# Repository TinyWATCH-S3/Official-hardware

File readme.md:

# TinyWATCH-S3 Official Hardware

In this repository, you will find all of the KiCAD design files for the official Unexpected Maker TinyWATCH-S3

**The current release version of the TinyWATCH S3 hardware is revision P10.**

Please note that the license for these design files is the CERN Open Hardware Licence v1.2, which requires any use of these design files to be also kept fully open source under the same license.

So though you are free to use these files in your own projects, and even commercialise them, the "thing" you make must be open source and shared with the community.

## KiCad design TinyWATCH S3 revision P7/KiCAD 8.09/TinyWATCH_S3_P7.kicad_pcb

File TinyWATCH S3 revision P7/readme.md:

# TinyWATCH-S3 revision P7

I've made my best efforts to ensure consistency between the PCB layout and Schematic in terms of component values and packages.

Many footprints in the design reference non-standard (library) footprints, and I don't offer a library for them as they are already embedded in PCB layout anyway. 

If you do find any other inconsistencies, please create a PR, or raise an issue, thanks :)

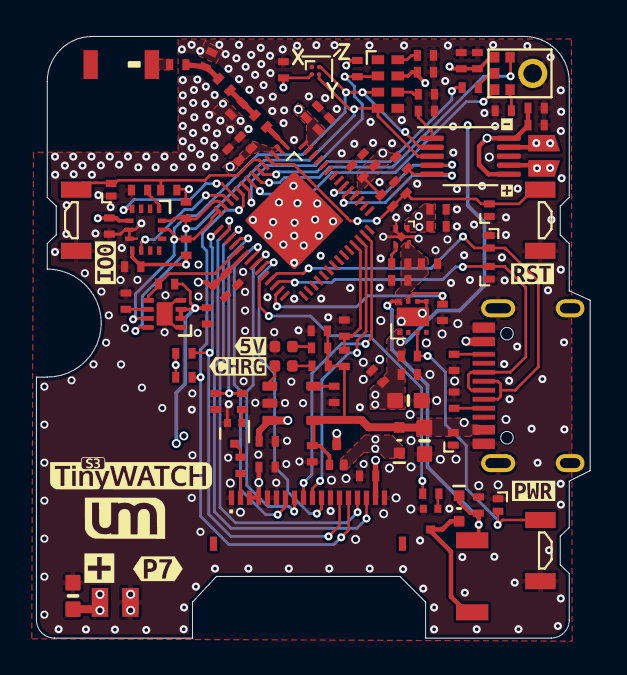
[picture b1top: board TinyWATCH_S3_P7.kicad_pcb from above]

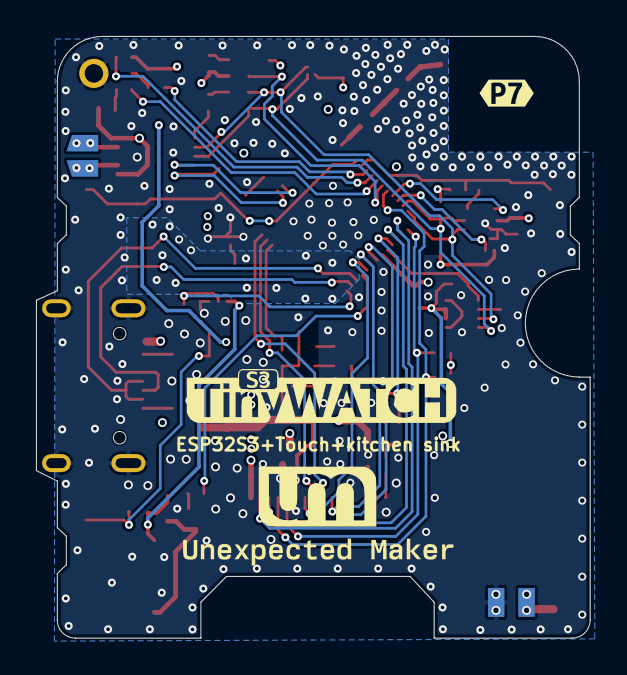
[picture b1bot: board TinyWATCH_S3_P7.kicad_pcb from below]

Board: 4 copper layers, 30.8 x 33.4 mm, 115 parts (3 on the bottom side), 60 nets.

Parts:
AF1: 3.6pF; _0402_SRN
AF2: 1.5nH; _0402_SRN
AF3: 2.4nH; _0402_SRN
BAT1: LIPO; HapticMotor_Solder_Pads
C1, C4, C6, C8, C10, C11, C12, C13, C14, C16, C17, C19, C22, C23, C31: 0.1uF; _0402_SRN
C2, C3, C9, C15, C18, C20, C24, C25, C27, C30, C33: 1uF; _0402_SRN
C5: 1.0pF; _0402_SRN
C7, C21, C28: 10uF; _0603MP
C26: 220pF; _0402_SRN
C29, C32, C34: 2.2uF; _0402_SRN
CHRG2: TP4065-4.2V-SOT25-R; SOT23-5-SML2
D1, D2, D4, D9, D10, D11: D_TVS; TVS X1-DFN1006-2-BEST
D3: ORANGE; LED_0402_1005Metric
D5: DIODE-SCHOTTKYWIDE; SOD-523-MSK4010
D6: DIODESOD-123; SOD-523-MSK4010
D8: RED; LED_0402_1005Metric
IC2: ESP32-S3REV0-SILICON; QFN56-ESP32-S3-PROD-THIN
IC3: XC6194AA03ER-G; XC6194BANNERG
IC4: ICS_43434; ICS43434
J1: Conn_01x02_Pin; HapticMotor_Solder_Pads
J2: USB_C; USB-C-16P-LESSPASTE-2-FIxed
J3: Conn_01x18_Pin; JUSHUO AFH34-S18FIA-1H
L1: 3.3nH; _0402_SRN
Q1: MMBT2222; SOT-723
Q2: 600mA/40V; SOT-723
R1, R9, R11, R15: 5.1K; _0402_SRN
R2: 2K; _0402_SRN
R3, R16: 3K3; _0402_SRN
R4, R5, R6, R12, R25, R28, R29, R33: 10K; _0402_SRN
R7, R8, R10, R13, R14, R17, R18, R21, R22, R23, R30: 100K; _0402_SRN
R19: 1K; _0402_SRN
R20: 22; _0402_SRN
R26: 68; _0402_SRN
R27: 1k2; _0402_SRN
SP1: Speaker; MagneticBuzzer_KLJ-4020
SW1, SW3, SW5: SW_Push; SW_SPST_B3U-3000P
T1, T1#2: Tab
T3: P-FET; SOT723
U1: RV-3028-C7-32.768KHZ; IC_RV-3028-C7-32.768KHZ-1PPM-TA-QA
U2: MMC5603NJL; WLP-4_0.83x0.83mm_P0.4mm
U3: NCP167BMX330TBG; VREG_NCP170AMX300TCG
U4: MAX17048G+T10; MAX17048G_T10_SON50P200X200X80-9N
U5: DRV2605LDGSR; VSSOP-10_3x3mm_P0.5mm
U$1: BMI270
U$13: FRACTUS_FR05-S1-N-0-102-LEAN; ANT_2450AT18B100E
U$88: UM_LOGONEW_SMALLER; UM_LOGO_NEW_TINY
U$88#2: UM_LOGONEW_SMALLER; UM_LOGO_NEW_SMALL
kibuzzard-64F95D11: G***; kibuzzard-64F95D11
kibuzzard-64F95D18: G***; kibuzzard-64F95D18
kibuzzard-65BEEB54: G***; kibuzzard-65BEEB54
kibuzzard-65BEEBBF: G***; kibuzzard-65BEEBBF
kibuzzard-65BF212E: G***; kibuzzard-65BF212E
kibuzzard-664EFB11: G***; kibuzzard-664EFB11
kibuzzard-664EFB60: G***; kibuzzard-664EFB60
kibuzzard-6518A76D: G***; kibuzzard-6518A76D
kibuzzard-6518A765: G***; kibuzzard-6518A765
kibuzzard-6534A245: G***; kibuzzard-6534A245
kibuzzard-664315DB: G***; kibuzzard-664315DB

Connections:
3.3V: C1.1, C2.1, C8.1, C9.1, C11.1, C12.1, C13.1, C14.1, C15.1, C16.1, C17.1, C18.1, C19.1, C20.1, C24.1, C26.1, C31.1, C33.1, C34.1, IC2.2 (VDDA3P3_1), IC2.3 (VDDA3P3_2), IC2.20 (VDD3P3_RTC), IC2.46 (VDD3P3_CPU), IC2.55 (VDDA_2), IC2.56 (VDDA_1), IC4.5 (VDD), J3.3, J3.4, J3.17, R4.1, R5.1, R7.1, R10.1, R14.1, R18.1, R28.1, R29.1, U2.B1 (VDD), U3.1 (OUT), U5.6 (VDD/NC), U5.10 (VDD), U$1.5 (VDDIO), U$1.8 (VDD)
/ANT: AF3.2, U$13.1
/ANT_FREQ: AF1.2, AF2.2, AF3.1
/ANT_MATCH: AF1.1, C5.2, L1.1
/BMA_INT1: IC2.11 (IO6), U$1.4 (INT1)
/BMA_INT2: IC2.12 (IO7), U$1.9 (INT2)
/BMI_ADR: R23.1, U$1.1 (SDO)
/BUZZ: D6.A, Q2.3 (C), SP1.-
/BUZZ_T: Q2.1 (B), R27.1
/CC1: J2.A5 (CC1), R11.2
/CC2: J2.B5 (CC2), R9.2
/D+: D2.2 (A2), IC2.26 (IO20/USB_D+), J2.A6 (D+), J2.B6 (D+)
/D-: D4.2 (A2), IC2.25 (IO19/USB_D-), J2.A7 (D-), J2.B7 (D-)
/HAP_EN: IC2.47 (MTDI), R18.2, U5.5 (EN)
/HAP_TRIG: IC2.48 (MTMS), U5.4 (IN/TRIG)
/IO0: D10.2 (A2), IC2.5 (IO0), R10.2, SW3.2
/IO5_SDA2: IC2.10 (IO5), J3.14, R29.2
/IO10_SCL2: IC2.15 (IO10), J3.13, R28.2
/IO18_BUZZ: IC2.24 (IO18), R27.2
/LDO_EN: R30.2, U3.3 (EN)
/LEDK: J3.2, R20.2
/LNA_IN: IC2.1 (LNA_IN), L1.2
/MIC_BCLK: IC2.7 (IO2), IC4.4 (BCLK)
/MIC_DATA: IC2.6 (IO1), R26.2
/MIC_SELECT: IC4.2 (SELECT), R13.2
/MIC_WS: IC2.8 (IO3), IC4.1 (WS)
/ON-SW: D9.2 (A2), IC3.3 (SW), R33.1, SW5.1
/OUT+: J1.1, U5.7 (OUT+)
/OUT-: J1.2, U5.9 (OUT-)
/PROG: CHRG2.5 (PROG), R16.1
/PWR-SHUTDOWN: IC2.27 (IO21), IC3.7 (SHDN), R25.1
/RESET: C3.1, D11.2 (A2), IC2.4 (CHIP_PU), R14.2, SW1.1
/RTC_EVI: R6.1, U1.8 (EVI)
/SCL: IC2.14 (IO9), R5.2, U1.3 (SCL), U2.A2 (SCL), U4.7 (SCL), U5.2 (SCL), U$1.13 (SCX)
/SDA: IC2.13 (IO8), R4.2, U1.4 (SDA), U2.B2 (SDA), U4.8 (SDA), U5.3 (SDA), U$1.14 (SDX)
/SPI_MO: IC2.40 (IO35), J3.10
/SPI_SCK: IC2.41 (IO36), J3.9
/STAT: CHRG2.1 (STAT), D3.P$2 (2)
/TCH_INT: IC2.16 (IO11), J3.16
/TCH_RST: IC2.17 (IO12), J3.15
/TFT_BACKLIGHT: IC2.18 (IO13), R12.1, R19.1
/TFT_CS: IC2.22 (IO16/XTAL_32K_N), J3.8
/TFT_DC: IC2.21 (IO15/XTAL_32K_P), J3.7
/TFT_RESET: IC2.23 (IO17), J3.11
/USB-5V: C27.1, C28.2, CHRG2.4 (VDD), D1.2 (A2), D5.A, J2.VBUS1 (VBUS), J2.VBUS2 (VBUS), R1.1, R2.1, R15.1, R17.1, T3.1 (G)
/VBUS: C23.1, C25.1, C29.1, D6.C, IC3.8 (VOUT), R30.1, SP1.+, U3.4 (IN)
/VBUS-IN: C10.1, C21.2, C22.1, C30.1, D5.C, IC3.1 (VIN), R33.2, T3.2 (S), U1.7 (VDD)
/VBUS_SENSE: IC2.39 (IO34), R2.2, R3.1
/~FG_ALERT: IC2.19 (IO14), R21.2, U4.5 (~ALERT)
/~FG_QSTRT: R22.1, U4.6 (QSTRT)
/~RTC_INT: IC2.9 (IO4), R7.2, U1.2 (~INT)
GND: AF2.1, BAT1.2, C1.2, C2.2, C3.2, C4.2, C5.1, C6.2, C7.2, C8.2, C9.2, C10.2, C11.2, C12.2, C13.2, C14.2, C15.2, C16.2, C17.2, C18.2, C19.2, C20.2, C21.1, C22.2, C23.2, C24.2, C25.2, C26.2, C27.2, C28.1, C29.2, C30.2, C31.2, C32.2, C33.2, C34.2, CHRG2.2 (VSS), D1.1 (A1), D2.1 (A1), D4.1 (A1), D8.P$2 (2), D9.1 (A1), D10.1 (A1), D11.1 (A1), IC2.EXP (GNDPAD), IC3.5 (VSS), IC3.6 (TEST), IC3.9 (EP), IC4.3 (GND), J2.GND, J2.GND2 (GND), J2.SHLD, J3.1, J3.5, J3.6, J3.12, J3.18, Q1.2 (E), Q2.2 (E), R3.2, R6.2, R8.2, R9.1, R11.1, R12.2, R13.1, R16.2, R17.2, R22.2, R23.2, R25.2, SW1.2, SW3.1, SW5.2, U1.5 (VSS), U2.A1 (VSA), U3.2 (GND), U3.5 (EXP), U4.1 (CTG), U4.4 (GND), U4.9 (EP), U5.8 (GND), U$1.6 (GNDIO), U$1.7 (GND)
unnamed: C4.1, U5.1 (REG)
unnamed: D3.P$1 (1), R1.2
unnamed: D8.P$1 (1), R15.2
unnamed: IC4.6 (DATA), R26.1
unnamed: Q1.1 (B), R19.2
unnamed: Q1.3 (C), R20.1
unnamed: R8.1, U1.6 (VBACKUP)
VBAT: BAT1.1, C6.1, C7.1, C32.1, CHRG2.3 (VBAT), R21.1, T3.3 (D), U4.2 (CELL), U4.3 (VDD)

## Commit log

2024-01-20 Updated Schematic PDF Added KiCAD 7.0.10 design files Added ibom output
2024-01-20 Updated and added new readme cleaned up footprint naming
2024-01-20 Added KiCAD project file
2024-01-20 added 3d models that were referenced externally
2024-01-20 removed lock file from repo woops
2024-01-20 Added gitignore
2024-01-27 fixed MICRO/PICO Blade connector footrint description
2024-06-25 Start of P7 files
2025-03-12 Added P7 files for KiCAD Added P10 files for KiCAD
